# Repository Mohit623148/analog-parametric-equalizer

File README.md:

# 🎛️ 5-Band Analog Parametric Audio Equalizer

> A fully analog, State Variable Filter (SVF) based parametric equalizer covering the full audio spectrum (20 Hz – 20 kHz), designed as Minor Project II at NIT Andhra Pradesh.

---

## 📌 Project Overview

This project implements a **5-band analog parametric equalizer** using the **KHN (Kerwin-Huelsman-Newcomb) State Variable Filter** topology. It features independent control of center frequency, gain (±9 dB), and Q (bandwidth) for each band — without any cross-coupling between parameters.

The complete design flow covers:
- Transfer function derivation and circuit analysis
- LTspice behavioral and SPICE-level simulation
- Proteus verification with exact TL074CDR models
- KiCad schematic capture (EESchema) and 4-layer PCB layout (PCBnew)

---

## 🗂️ Repository Structure

```
analog-parametric-equalizer/
│
├── ltspice/                  # LTspice simulation files (.asc)
│   ├── full_circuit.asc      # Complete cascaded equalizer
│   ├── low_shelf.asc
│   ├── band1_250Hz.asc
│   ├── band2_800Hz.asc
│   ├── band3_2500Hz.asc
│   └── high_shelf.asc
│
├── kicad/                    # KiCad project files
│   ├── Mini_project.kicad_pro
│   ├── Mini_project.kicad_sch
│   ├── Mini_project.kicad_pcb
│   └── Mini_project.kicad_prl
│
├── docs/                     # Documentation
│   ├── Project_report.pdf    # Full 27-page project report
│   └── ppt_EQ.pptx           # Presentation slides
│
├── images/                   # Screenshots and renders
│   ├── ltspice_full_circuit.png
│   ├── kicad_schematic.png
│   ├── pcb_top_view.png
│   ├── pcb_3d_isometric.png
│   └── sim_smile_curve.png
│
└── README.md
```

---

## ⚙️ Filter Architecture

The equalizer uses a **cascaded (series)** signal chain — each filter block feeds the next, which simplifies gain staging and inter-band tuning.

```
Audio In (3.5mm TRRS)
    │
    ▼
[DC Block + Impedance Match]  →  [ESD Protection — TVS1400DRV]
    │
    ▼
[Low Shelf Filter]        fc: 120–500 Hz,    Gain: ±9 dB
    │
    ▼
[SVF Band 1 — Bass]       f₀: 120–500 Hz,   Gain: ±9 dB,  Q: adjustable
    │
    ▼
[SVF Band 2 — Midrange]   f₀: 400–1600 Hz,  Gain: ±9 dB,  Q: adjustable
    │
    ▼
[SVF Band 3 — Upper Mid]  f₀: 1.2–5 kHz,    Gain: ±9 dB,  Q: adjustable
    │
    ▼
[High Shelf Filter]        fc: 1.2–5 kHz,   Gain: ±9 dB
    │
    ▼
[Output Buffer + ESD]  →  Audio Out (3.5mm TRRS)
```

### Band Summary

| Band         | Center Freq | Tuning Range | Integrator Caps | Frequency Pot     |
|--------------|-------------|--------------|-----------------|-------------------|
| Low Shelf    | 120–500 Hz  | Adjustable   | C11 = 80 nF     | RV2 (100kΩ dual)  |
| Band 1 Bass  | 250 Hz      | 120–500 Hz   | C3, C4 = 33 nF  | RV3/RV4 (10kΩ dual)|
| Band 2 Mid   | 800 Hz      | 400–1600 Hz  | C7, C8 = 10 nF  | RV7/RV9 (10kΩ dual)|
| Band 3 Hi-Mid| 2.5 kHz     | 1.2–5 kHz    | C9, C10 = 3.3 nF| RV10/RV12 (10kΩ dual)|
| High Shelf   | 1.2–5 kHz   | Adjustable   | C2 = 6.8 nF     | RV15 (100kΩ dual) |

---

## 🔬 Key Design Achievements

### Q–Gain Decoupling
In a standard SVF, bandpass peak = Q × Vin, meaning tuning Q inadvertently changes the boost/cut magnitude. This was solved by relocating the Q-control resistor to the BP output feedback path of the summing amplifier — peak amplitude is now constant at Vin, fully independent of Q.

### Dual-Gang Frequency Control
Center frequency ω₀ = 1/(RC) requires both integrators to track the same R simultaneously. Dual-gang potentiometers ensure both integrators always see equal resistance, maintaining SVF symmetry at any frequency setting.

### SVF Bandpass Transfer Function

```
              (ω₀/Q) · s
H(s) = ─────────────────────────────
         s² + (ω₀/Q)·s + ω₀²
```

---

## 🧰 Components

**Core ICs:**
- `TL074CDR` — Quad JFET-input op-amp, SOIC-14 (×5, giving 20 op-amp stages)
- `TVS1400DRV` — TVS ESD protection array (×2, at input and output)

**Op-Amp Key Specs (TL074CDR):**

| Parameter       | Value       |
|-----------------|-------------|
| Supply voltage  | ±15 V       |
| Slew rate       | 13 V/µs     |
| GBW product     | 3 MHz       |
| Input bias      | 65 pA       |
| Noise voltage   | 18 nV/√Hz   |

**Total BOM:** 89 components, 56 fixed resistors, 11 capacitors, 16 potentiometers, 2 audio connectors.

---

## 📊 Simulation Results

All five filter blocks were simulated in **LTspice XVII** (AC sweep, 20 Hz – 20 kHz, 1000 pts/decade) and verified in **Proteus** using exact TL074CDR SPICE models.

| Block          | Target f₀/fc   | Result                  | Gain Range   | Status  |
|----------------|----------------|-------------------------|--------------|---------|
| Low Shelf      | 250 Hz nominal | ~250 Hz, tunable 120–500 Hz | ±9 dB   | ✅ Pass |
| Band 1 (Bass)  | 250 Hz         | ~250 Hz, tunable 120–500 Hz | ±9 dB   | ✅ Pass |
| Band 2 (Mid)   | 800 Hz         | ~800 Hz, tunable 400–1600 Hz| ±9 dB   | ✅ Pass |
| Band 3 (Hi-Mid)| 2.5 kHz        | ~2.5 kHz, tunable 1.2–5 kHz | ±9 dB  | ✅ Pass |
| High Shelf     | 2.3 kHz nominal| ~2.3 kHz, tunable 1.2–5 kHz | ±9 dB  | ✅ Pass |

**Preset EQ responses verified:** V-Shape (Smile Curve), Vocal Boost

---

## 🖥️ PCB Design

Designed in **KiCad PCBnew v9.0** with a 4-layer FR-4 stackup:

| Layer      | Role                                  |
|------------|---------------------------------------|
| F.Cu (Top) | Signal routing, component placement   |
| In1.Cu     | Solid GND plane                       |
| In2.Cu     | ±15 V power distribution              |
| B.Cu (Bot) | Secondary signal routing              |

**PCB Stats:** 1,468 track segments · 150 vias · A3 drawing sheet

Layout follows signal-flow order (left → right), with decoupling caps adjacent to op-amp supply pins and all potentiometers along one edge for front-panel mounting.

---

## 🛠️ Tools Used

| Tool              | Version | Purpose                       |
|-------------------|---------|-------------------------------|
| LTspice XVII      | —       | AC sweep simulation           |
| Proteus Design Suite | —    | SPICE verification            |
| KiCad EESchema    | 9.0     | Schematic capture             |
| KiCad PCBnew      | 9.0     | PCB layout                    |

---

## 👥 Team

| Name              | Roll No. |
|-------------------|----------|
| Mohit Kumar Gupta | 623148   |
| Satyam Kumar      | 623172   |
| Vishal Ray        | 622271   |

**Guide:** Dr. M. C. Raju, Assistant Professor, DECE, NIT Andhra Pradesh
**Course:** Minor Project II (EC399) · Academic Year 2025–26

---

## 📄 License

This project is shared for educational and reference purposes. Feel free to study, fork, and build upon it — attribution appreciated.

---

## 🔮 Future Work

- [ ] PCB fabrication and hardware assembly
- [ ] Audio characterisation using REW (THD+N, noise floor, dynamic range)
- [ ] Enclosure and front-panel design for all 16 potentiometers
- [ ] Expand to 7 or 10 bands with additional SVF stages
- [ ] PCB noise optimisation based on measured results

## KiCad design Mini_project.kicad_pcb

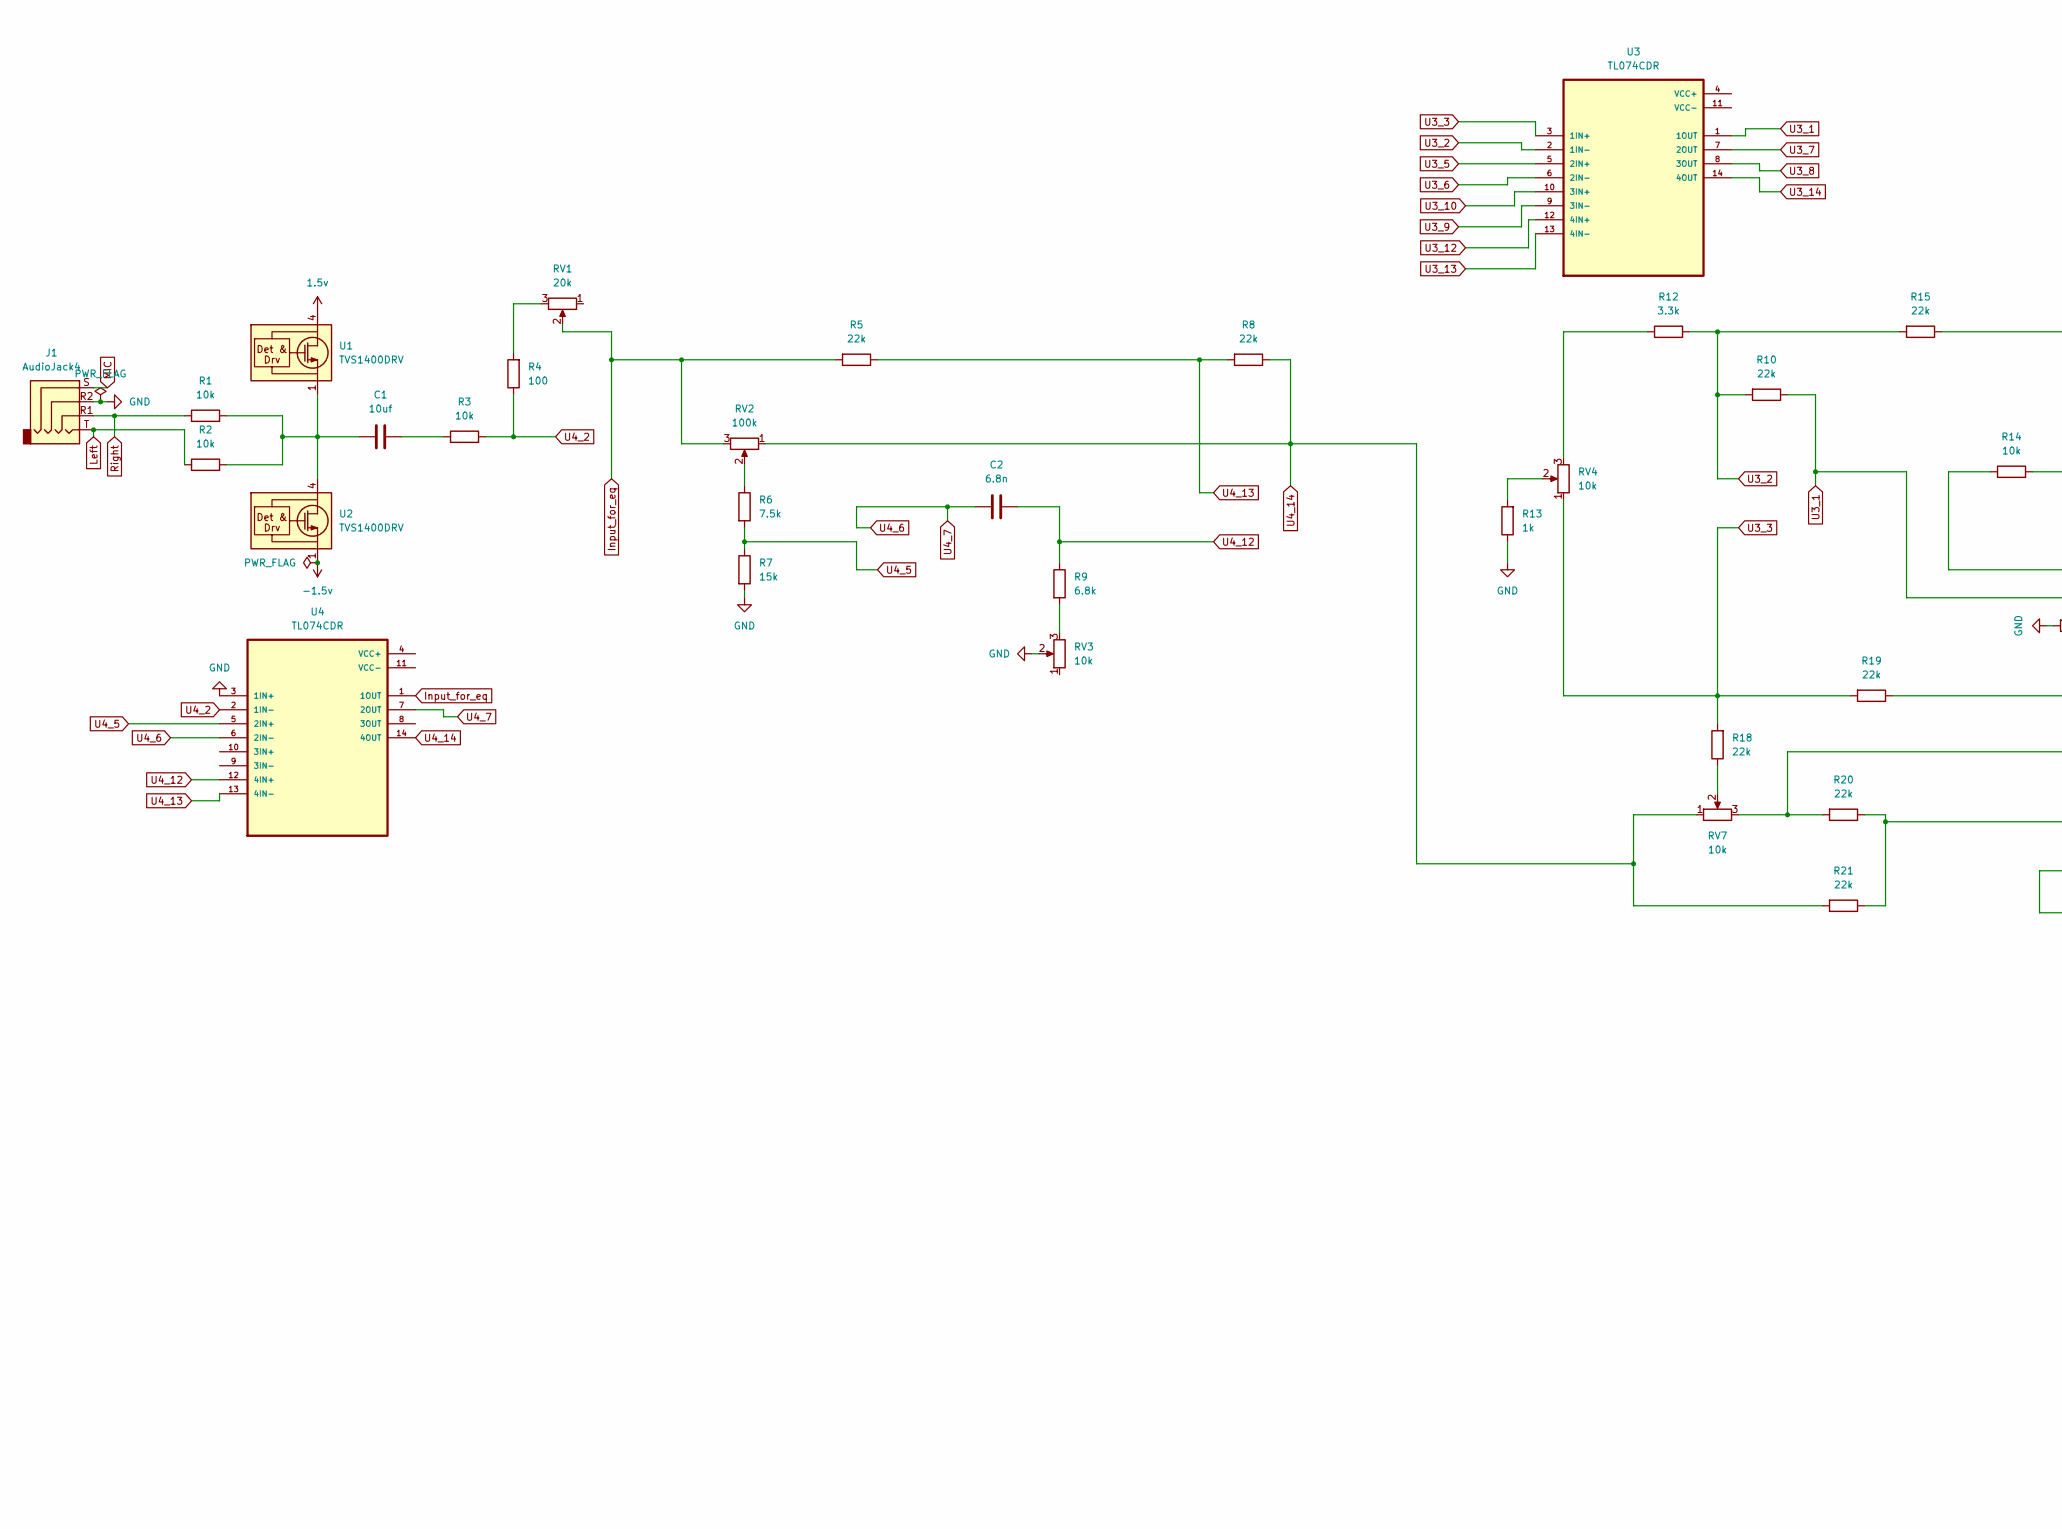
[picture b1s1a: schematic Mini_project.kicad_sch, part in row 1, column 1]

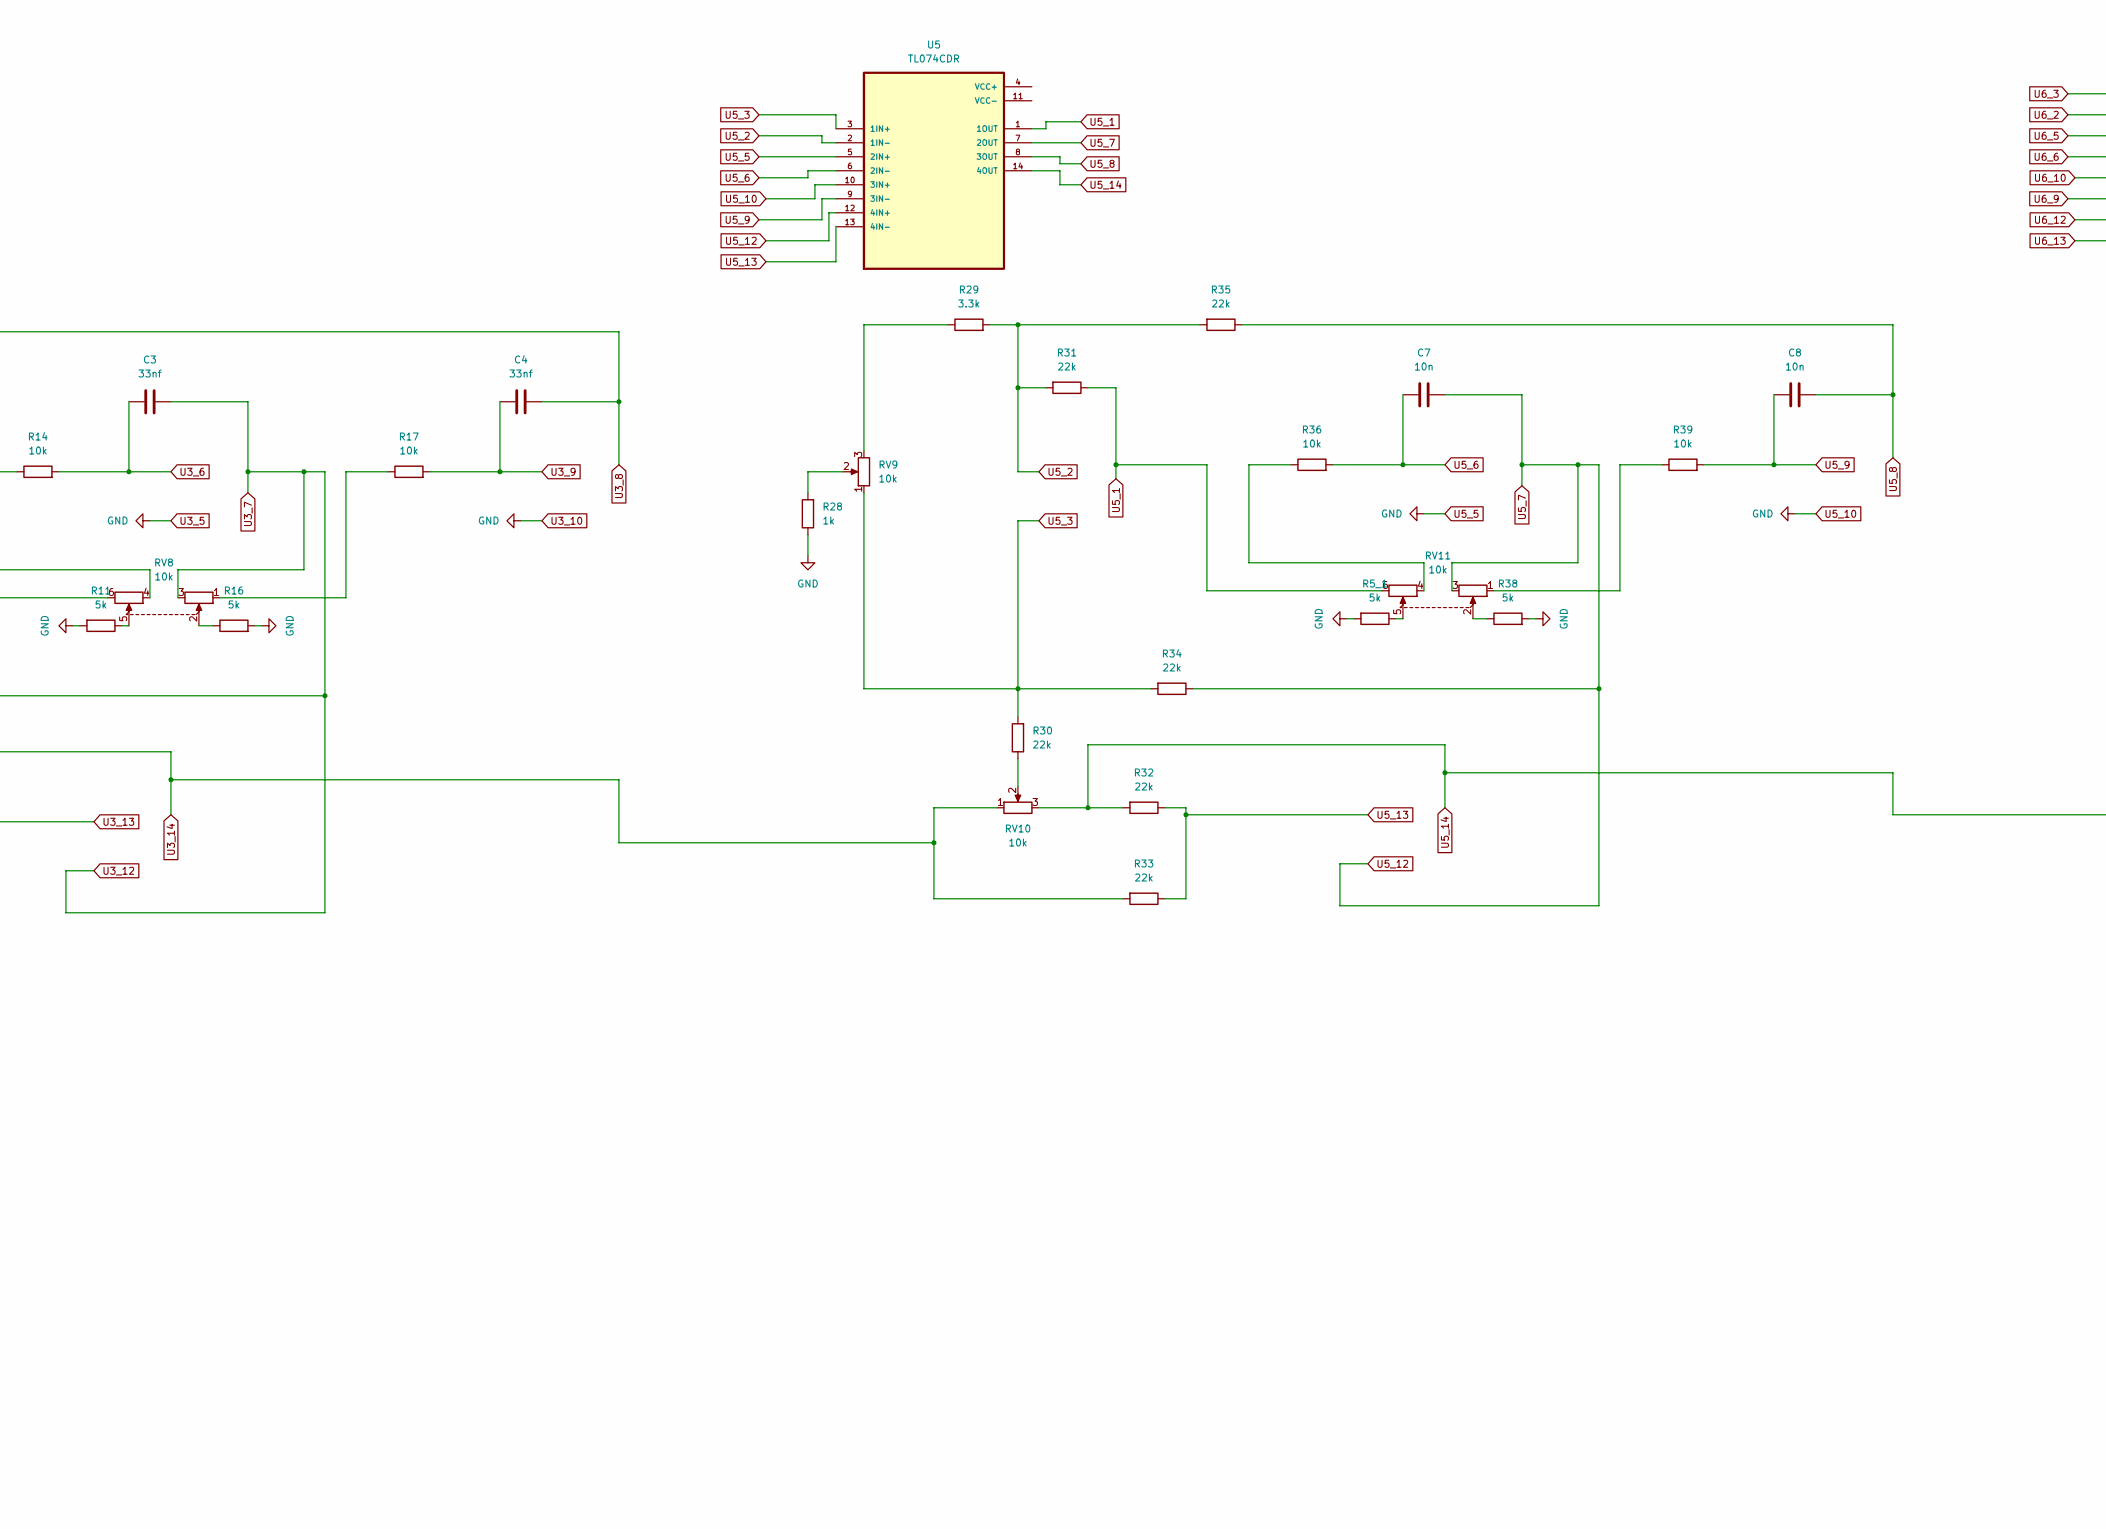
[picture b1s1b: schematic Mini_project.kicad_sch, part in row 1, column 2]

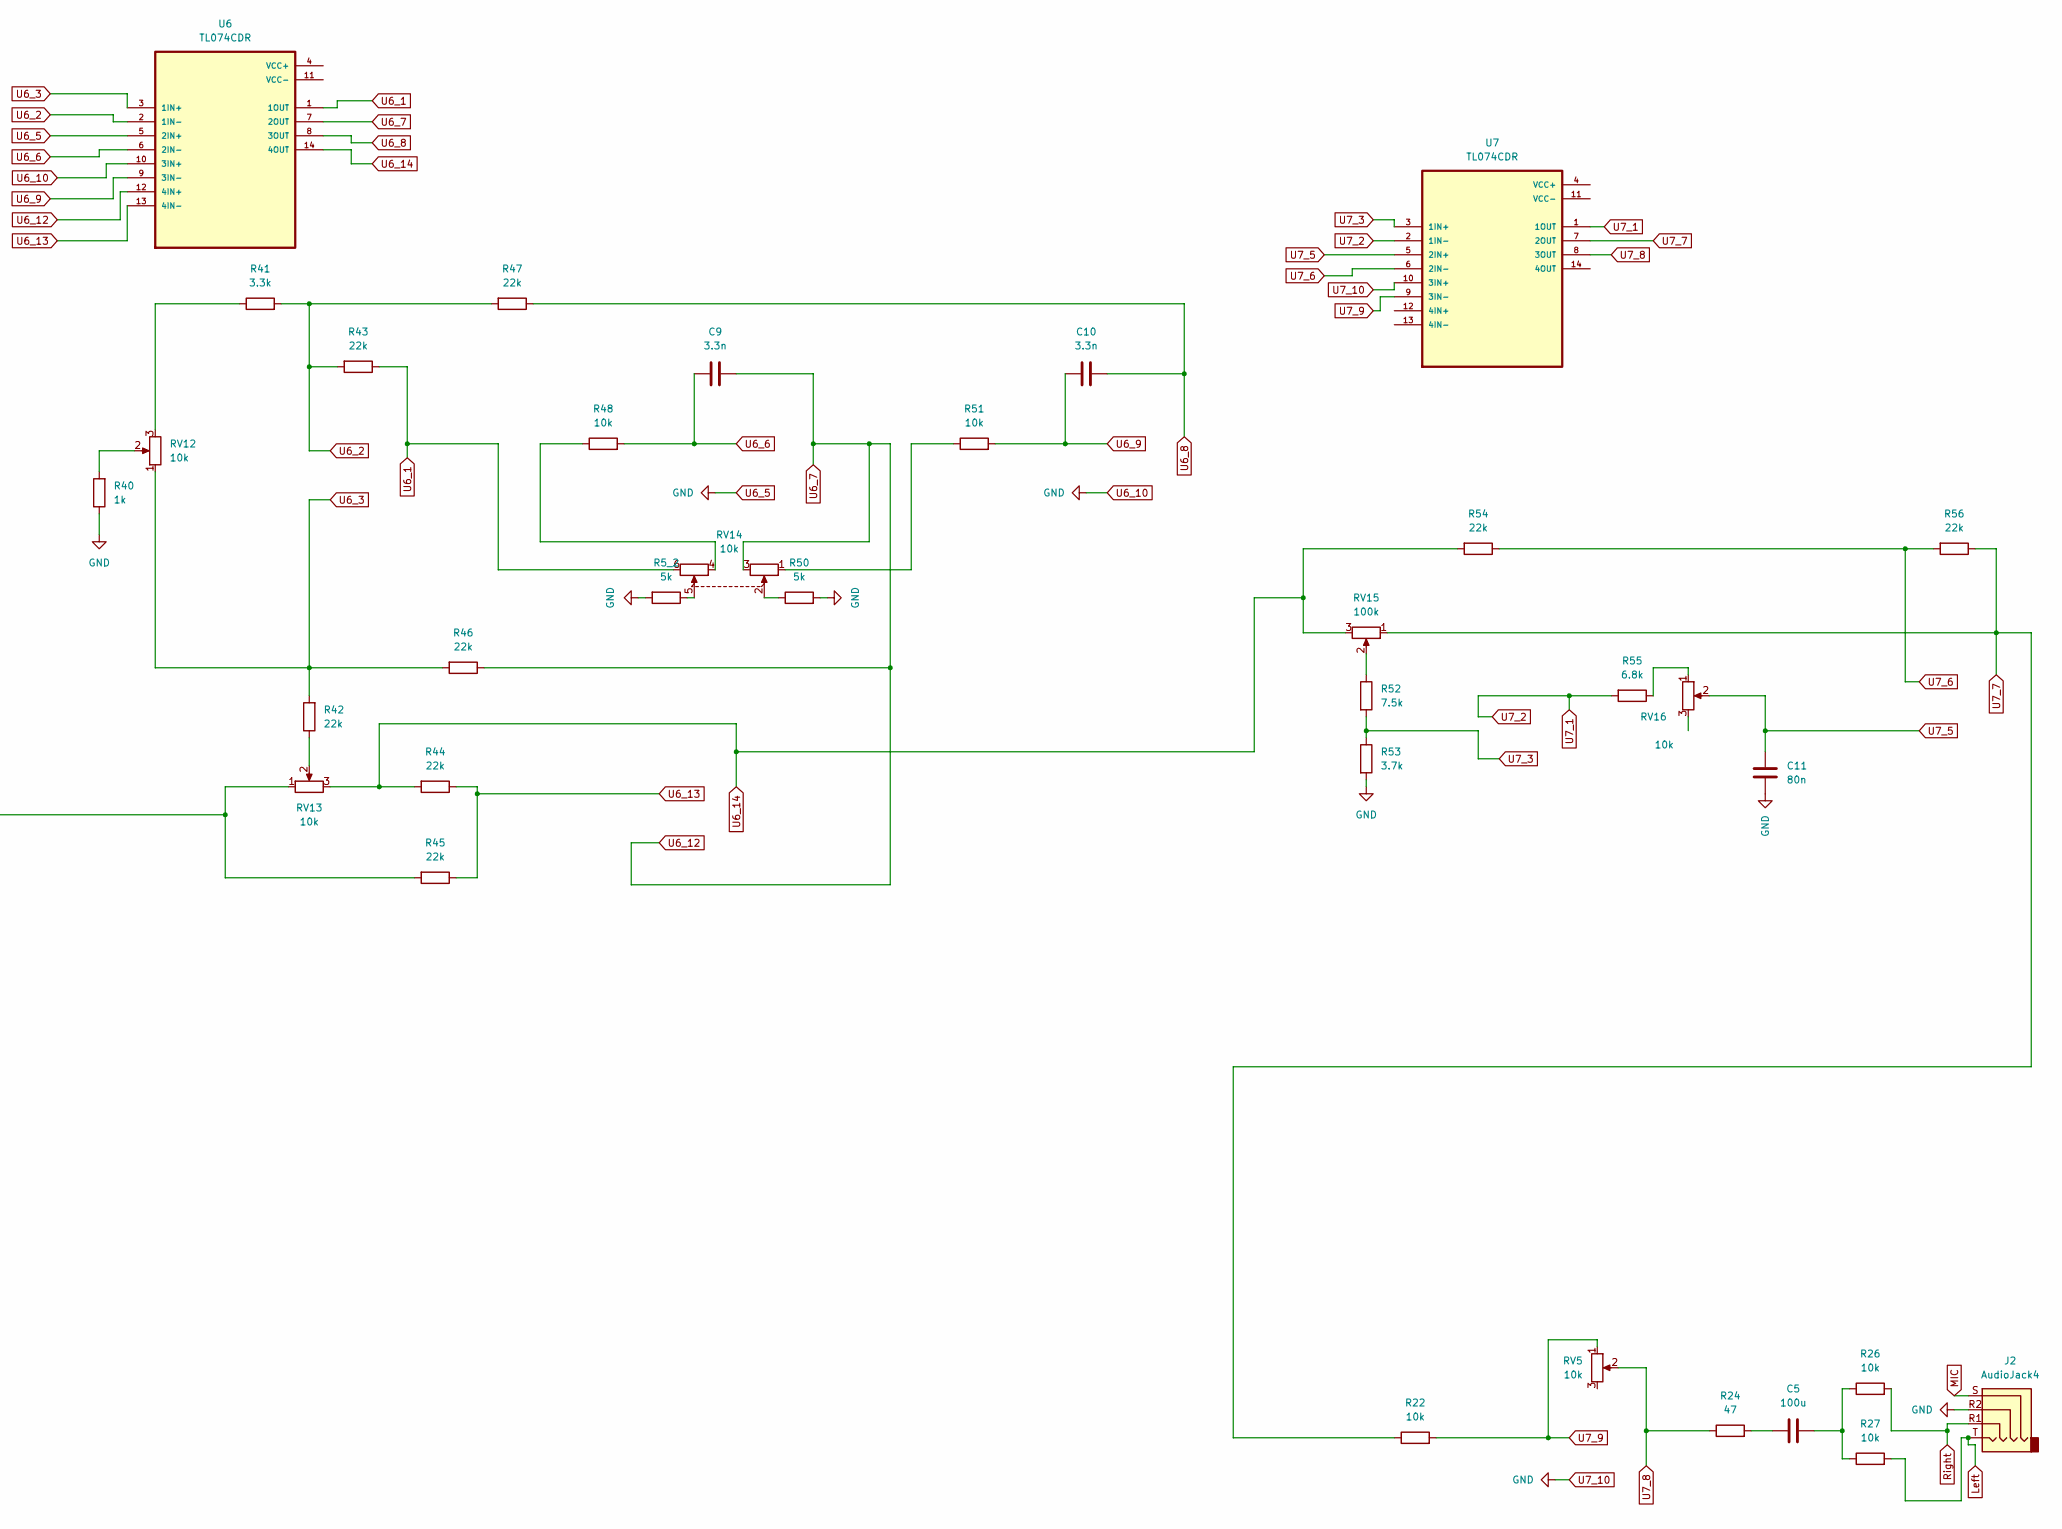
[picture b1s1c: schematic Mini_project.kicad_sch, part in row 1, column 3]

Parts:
C1: 10uf; C_Trimmer_Murata_TZC3
C2: 6.8n; C_Trimmer_Murata_TZC3
C3, C4: 33nf; C_Trimmer_Murata_TZC3
C5: 100u; C_Trimmer_Murata_TZC3
C7, C8: 10n; C_Trimmer_Murata_TZC3
C9, C10: 3.3n; C_Trimmer_Murata_TZC3
C11: 80n; C_Trimmer_Murata_TZC3
J1, J2: AudioJack4; Jack_3.5mm_CUI_SJ-3524-SMT_Horizontal
R1, R2, R3, R14, R17, R22, R26, R27, R36, R39, R48, R51: 10k; R_0805_2012Metric
R4: 100; R_0805_2012Metric
R5, R8, R10, R15, R18, R19, R20, R21, R30, R31, R32, R33, R34, R35, R42, R43, R44, R45, R46, R47, R54, R56: 22k; R_0805_2012Metric
R5_1, R5_2, R11, R16, R38, R50: 5k; R_0805_2012Metric
R6, R52: 7.5k; R_0805_2012Metric
R7: 15k; R_0805_2012Metric
R9, R55: 6.8k; R_0805_2012Metric
R12, R29, R41: 3.3k; R_0805_2012Metric
R13, R28, R40: 1k; R_0805_2012Metric
R24: 47; R_0805_2012Metric
R53: 3.7k; R_0805_2012Metric
RV1: 20k; Potentiometer_Alpha_RD901F-40-00D_Single_Vertical
RV2, RV15: 100k; Potentiometer_Alpha_RD901F-40-00D_Single_Vertical
RV3, RV4, RV5, RV7, RV9, RV10, RV12, RV13, RV16: 10k; Potentiometer_Alpha_RD901F-40-00D_Single_Vertical
RV8, RV11, RV14: 10k; Potentiometer_Alpha_RD902F-40-00D_Dual_Vertical
U1, U2: TVS1400DRV; WSON-6-1EP_2x2mm_P0.65mm_EP1x1.6mm
U3, U4, U5, U6, U7: TL074CDR; SOIC127P600X175-14N

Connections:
1.5v: U1.4 (IN), U1.5 (IN), U1.6 (IN)
-1.5v: U2.1 (GND), U2.2 (GND), U2.3 (GND), U2.7 (GND)
Input_for_eq: R5.2, RV1.2, RV2.3, U4.1 (1OUT)
Left: J1.T, J2.T, R2.1, R27.2
MIC: J1.S, J2.S
unnamed: C1.1, R1.2, R2.2, U1.1 (GND), U1.2 (GND), U1.3 (GND), U1.7 (GND), U2.4 (IN), U2.5 (IN), U2.6 (IN)
unnamed: C1.2, R3.1
unnamed: C5.1, R24.2
unnamed: C5.2, R26.1, R27.1
unnamed: R4.2, RV1.3
unnamed: R5_1.1, RV11.5
unnamed: R5_2.1, RV14.5
unnamed: R6.1, RV2.2
unnamed: R9.2, RV3.3
unnamed: R11.1, RV8.5
unnamed: R12.1, RV4.3
unnamed: R13.2, RV4.2
unnamed: R14.1, RV8.4
unnamed: R16.1, RV8.2
unnamed: R17.1, RV8.1
unnamed: R18.1, RV7.2
unnamed: R28.2, RV9.2
unnamed: R29.1, RV9.3
unnamed: R30.1, RV10.2
unnamed: R36.1, RV11.4
unnamed: R38.1, RV11.2
unnamed: R39.1, RV11.1
unnamed: R40.2, RV12.2
unnamed: R41.1, RV12.3
unnamed: R42.1, RV13.2
unnamed: R48.1, RV14.4
unnamed: R50.1, RV14.2
unnamed: R51.1, RV14.1
unnamed: R52.1, RV15.2
unnamed: R55.1, RV16.1
Right: J1.R1, J2.R1, R1.1, R26.2
U3_1: R10.1, RV8.6, U3.1 (1OUT)
U3_2: R10.2, R12.2, R15.2, U3.2 (1IN-)
U3_3: R18.2, R19.2, RV4.1, U3.3 (1IN+)
U3_6: C3.1, R14.2, U3.6 (2IN-)
U3_8: C4.2, R15.1, U3.8 (3OUT)
U3_9: C4.1, R17.2, U3.9 (3IN-)
U3_10: C11.1, J1.R2, J2.R2, R5_1.2, R5_2.2, R7.2, R11.2, R13.1, R16.2, R28.1, R38.2, R40.1, R50.2, R53.2, RV3.2, U3.5 (2IN+), U3.10 (3IN+), U4.3 (1IN+), U5.5 (2IN+), U5.10 (3IN+), U6.5 (2IN+), U6.10 (3IN+), U7.10 (3IN+)
U3_12: C3.2, R19.1, RV8.3, U3.7 (2OUT), U3.12 (4IN+)
U3_13: R20.1, R21.1, U3.13 (4IN-)
U3_14: R20.2, R33.2, RV7.3, RV10.1, U3.14 (4OUT)
U4_2: R3.2, R4.1, U4.2 (1IN-)
U4_5: R6.2, R7.1, U4.5 (2IN+)
U4_6: C2.1, U4.6 (2IN-), U4.7 (2OUT)
U4_12: C2.2, R9.1, U4.12 (4IN+)
U4_13: R5.1, R8.2, U4.13 (4IN-)
U4_14: R8.1, R21.2, RV2.1, RV7.1, U4.14 (4OUT)
U5_1: R31.1, RV11.6, U5.1 (1OUT)
U5_2: R29.2, R31.2, R35.2, U5.2 (1IN-)
U5_3: R30.2, R34.2, RV9.1, U5.3 (1IN+)
U5_6: C7.1, R36.2, U5.6 (2IN-)
U5_8: C8.2, R35.1, U5.8 (3OUT)
U5_9: C8.1, R39.2, U5.9 (3IN-)
U5_12: C7.2, R34.1, RV11.3, U5.7 (2OUT), U5.12 (4IN+)
U5_13: R32.1, R33.1, U5.13 (4IN-)
U5_14: R32.2, R45.2, RV10.3, RV13.1, U5.14 (4OUT)
U6_1: R43.1, RV14.6, U6.1 (1OUT)
U6_2: R41.2, R43.2, R47.2, U6.2 (1IN-)
U6_3: R42.2, R46.2, RV12.1, U6.3 (1IN+)
U6_6: C9.1, R48.2, U6.6 (2IN-)
U6_8: C10.2, R47.1, U6.8 (3OUT)
U6_9: C10.1, R51.2, U6.9 (3IN-)
U6_12: C9.2, R46.1, RV14.3, U6.7 (2OUT), U6.12 (4IN+)
U6_13: R44.1, R45.1, U6.13 (4IN-)
U6_14: R44.2, R54.2, RV13.3, RV15.3, U6.14 (4OUT)
U7_1: R55.2, U7.1 (1OUT), U7.2 (1IN-)
U7_3: R52.2, R53.1, U7.3 (1IN+)
U7_5: C11.2, RV16.2, U7.5 (2IN+)
U7_6: R54.1, R56.2, U7.6 (2IN-)
U7_7: R22.1, R56.1, RV15.1, U7.7 (2OUT)
U7_8: R24.1, RV5.2, U7.8 (3OUT)
U7_9: R22.2, RV5.1, U7.9 (3IN-)

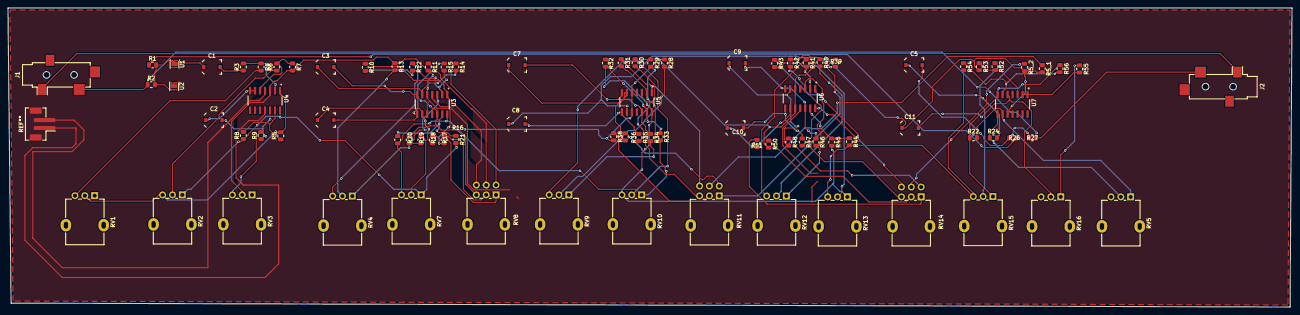
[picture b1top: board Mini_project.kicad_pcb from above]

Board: 4 copper layers, 326.3 x 76.0 mm, 88 parts (0 on the bottom side), 77 nets.

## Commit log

2026-06-27 Add project files — LTspice, KiCad schematic, PCB, report
